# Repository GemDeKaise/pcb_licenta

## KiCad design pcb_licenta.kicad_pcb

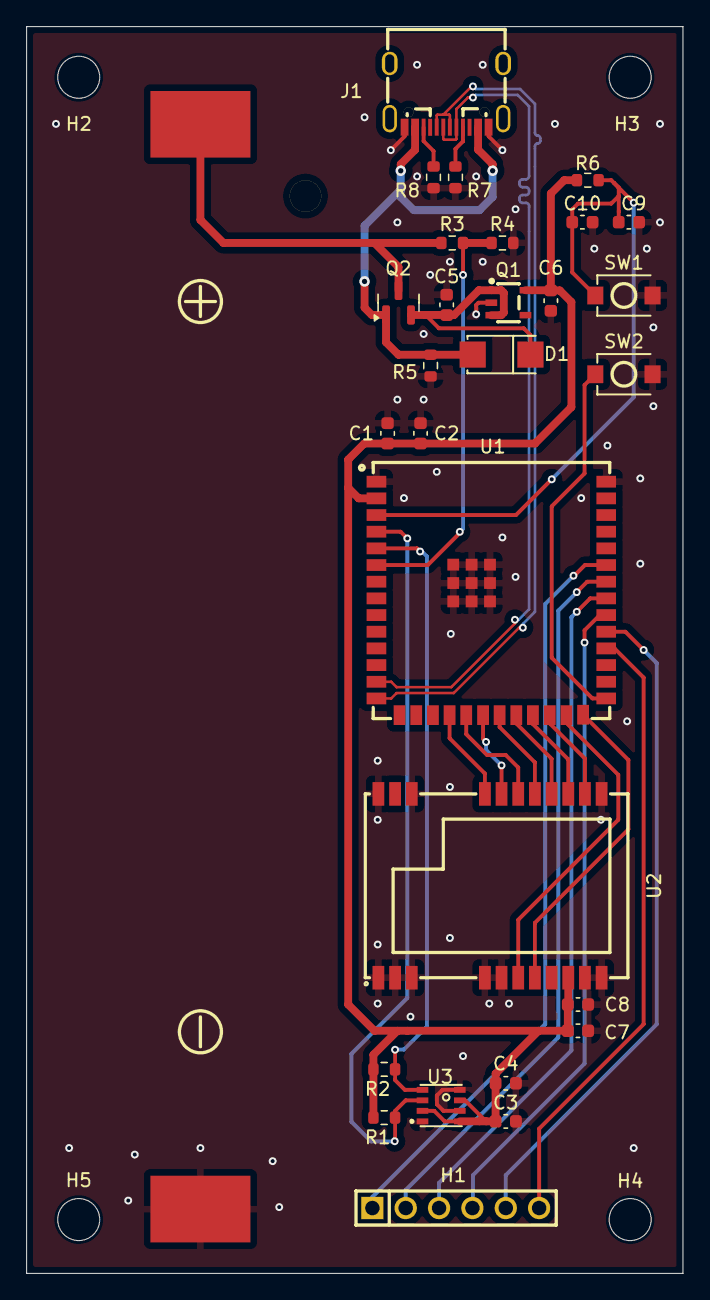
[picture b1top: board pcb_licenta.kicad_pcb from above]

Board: 2 copper layers, 50.0 x 95.0 mm, 33 parts (0 on the bottom side), 29 nets.

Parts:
BT1: BH-18650-B1BA002; BATTERY-SMD_18650-1S-L77.1-W20.7-1
C1, C3, C4, C8, C10: 100nF; C_0603_1608Metric
C2: 10uF; C_0603_1608Metric
C5, C6: 4.7uF; C_0603_1608Metric
C7: 22uF; C_0603_1608Metric
C9: 1uF; C_0603_1608Metric
D1: SS34_C8678; SMA_L4.3-W2.6-LS5.2-RD
H1: PZ254V-11-06P; HDR-TH_6P-P2.54-V-M
H2, H3, H4, H5: MountingHole; MountingHole_3.2mm_M3
J1: USB_C_Receptacle_USB2.0_16P; USB-C-SMD_TYPE-C-USB-17
Q1: XC6220B331MR-G; SOT-25_L3.0-W1.6-P0.95-LS2.8-TL
Q2: AO3401A; SOT-23
R1, R2, R6: 10k; R_0603_1608Metric
R3: 1M; R_0603_1608Metric
R4: 330k; R_0603_1608Metric
R5: 100k; R_0603_1608Metric
R7, R8: 5.1k; R_0603_1608Metric
SW1, SW2: TS-1088-AR02016; SW-SMD_L3.9-W3.0-P4.45
U1: ESP32-S3-WROOM-1U; WIRELM-SMD_ESP32-S3-WROOM-1U
U2: E22-900M22S; WIRELM-SMD_E22-900M22S
U3: BME688_C3664478; LGA-8_L3.0-W3.0-P0.80_BME688

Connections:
+3V3: C1.1, C2.1, C3.1, C4.2, C6.2, C7.1, C8.1, Q1.5 (VOUT), R1.1, R2.1, R6.1, U1.2 (3V3), U2.9 (VCC), U3.2 (CSB), U3.6 (VDDIO), U3.8 (VDD)
ADC_BAT: R3.2, R4.1, U1.6 (IO6)
BOOT: SW2.1, U1.27 (IO0)
BUSY: U1.23 (IO21), U2.14 (BUSY)
D+: J1.A6 (D+), J1.B6 (D+), U1.14 (IO20)
D-: J1.A7 (D-), J1.B7 (D-), U1.13 (IO19)
DIO1: U1.24 (IO47), U2.13 (DIO1)
EN: C9.1, C10.1, R6.2, SW1.1, U1.3 (EN)
GND: BT1.1, C1.2, C2.2, C3.2, C4.1, C5.2, C6.1, C7.2, C8.2, C9.2, C10.2, J1.A1 (GND), J1.A12 (GND), Q1.2 (VSS), R4.2, R5.1, R7.2, R8.2, SW1.2, SW2.2, U1.1 (GND), U1.40 (GND), U1.41 (GND), U2.1 (GND), U2.2 (GND), U2.3 (GND), U2.4 (GND), U2.5 (GND), U2.10 (GND), U2.11 (GND), U2.12 (GND), U2.20 (GND), U2.22 (GND), U3.1 (GND), U3.5 (SDO), U3.7 (GND)
MISO: U1.21 (IO13), U2.16 (MISO)
MOSI: U1.19 (IO11), U2.17 (MOSI)
NRST: U1.22 (IO14), U2.15 (NRST)
NSS: U1.18 (IO10), U2.19 (NSS)
unnamed: C5.1, D1.1 (K), Q1.1 (VIN), Q1.3 (CE), Q2.2 (S)
unnamed: J1.A5 (CC1), R7.1
unnamed: J1.B5 (CC2), R8.1
unnamed: H1.6, U1.30 (IO37)
unnamed: H1.5, U1.31 (IO38)
unnamed: H1.4, U1.32 (IO39)
unnamed: H1.3, U1.33 (IO40)
unnamed: H1.2, U1.34 (IO41)
unnamed: H1.1, U1.35 (IO42)
RXEN: U1.25 (IO48), U2.6 (RXEN)
SCK: U1.20 (IO12), U2.18 (SCK)
SCL: R2.2, U1.5 (IO5), U3.4 (SCK)
SDA: R1.2, U1.4 (IO4), U3.3 (SDI)
TXEN: U1.26 (IO45), U2.7 (TXEN)
VBAT: BT1.2, Q2.3 (D), R3.1
VBUS: D1.2 (A), J1.A4 (VBUS), J1.A9 (VBUS), Q2.1 (G), R5.2

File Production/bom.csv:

Designator,Footprint,Quantity,Value,LCSC Part #
"BOOT, ENBLE",SW-SMD_L3.9-W3.0-P4.45,2,TS-1088-AR02016,C720477
BT1,BATTERY-SMD_18650-1S-L77.1-W20.7-1,1,BH-18650-B1BA002,C2988620
"C1, C10, C3, C4, C8",0201,5,100nF,
C2,0805,1,10uF,
"C5, C6",0201,2,4.7uF,
C7,0201,1,22uF,
C9,0201,1,1uF,
D1,SMA_L4.3-W2.6-LS5.2-RD,1,SS34_C8678,C8678
H1,HDR-TH_6P-P2.54-V-M,1,PZ254V-11-06P,C492405
J1,USB_C_Receptacle_G-Switch_GT-USB-7010ASV,1,USB_C_Receptacle_USB2.0_16P,
Q1,SOT-25_L3.0-W1.6-P0.95-LS2.8-TL,1,XC6220B331MR-G,C86534
Q2,SOT-23,1,AO3401A,
"R1, R2, R6",0201,3,10k,
R3,0603,1,1M,
R4,0603,1,330k,
R5,0603,1,100k,
"R7, R8",0201,2,5.1k,
U1,WIRELM-SMD_ESP32-S3-WROOM-1U,1,ESP32-S3-WROOM-1U,C9900027631
U2,WIRELM-SMD_E22-900M22S,1,E22-900M22S,C411293
U3,LGA-8_L3.0-W3.0-P0.80_BME688,1,BME688_C3664478,C3664478

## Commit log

2025-03-29 Created some components
2025-03-29 Finalized schematic
2025-03-31 VERSION 1
2025-04-03 First revision
2025-04-07 Changed Usb-c
2025-04-07 Updated the 3d-models
